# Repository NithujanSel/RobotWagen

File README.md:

# RobotWagen
SmartSytems Project

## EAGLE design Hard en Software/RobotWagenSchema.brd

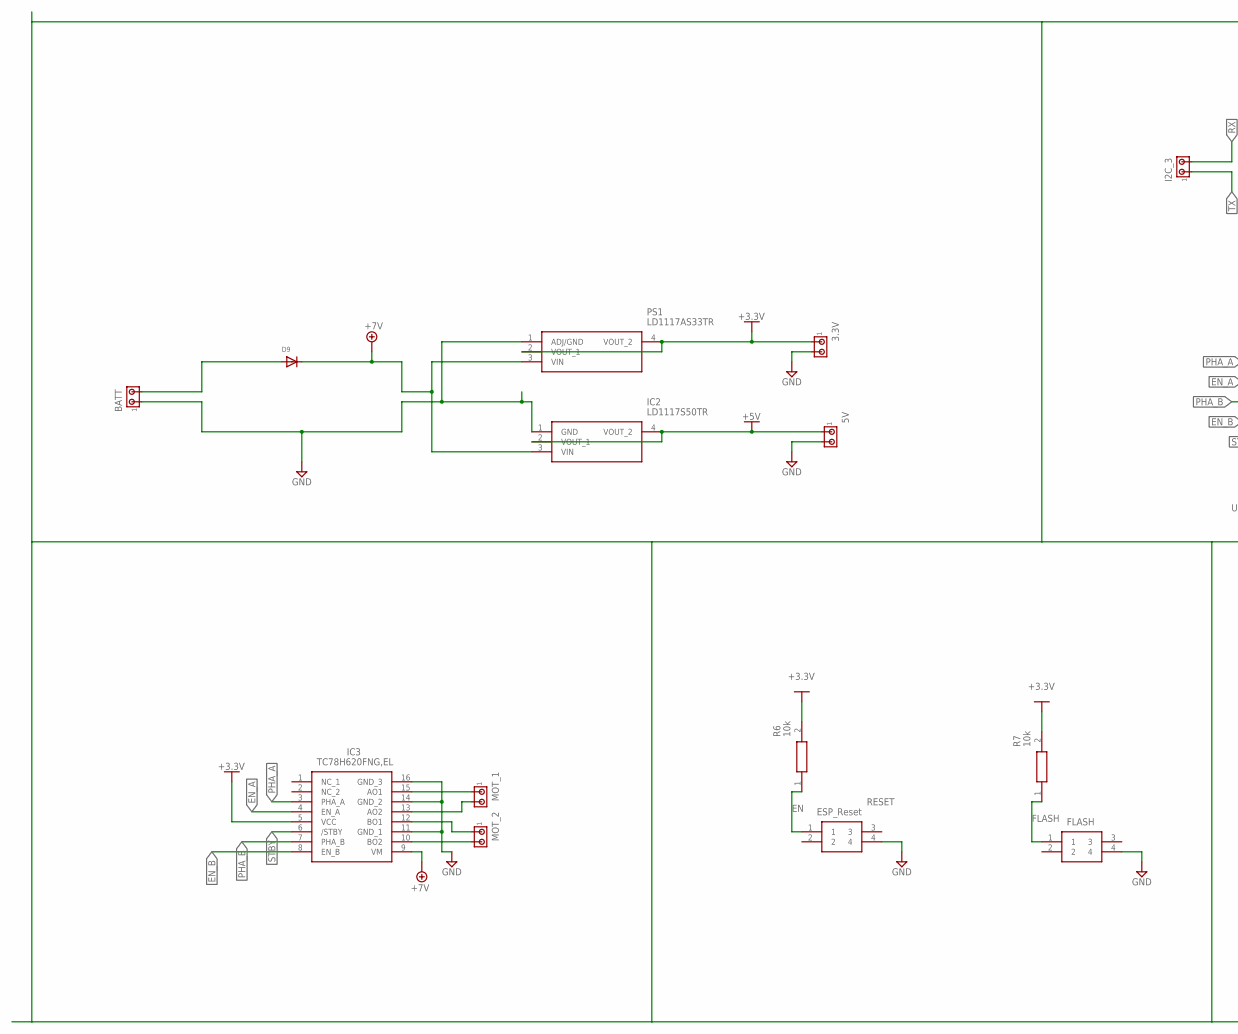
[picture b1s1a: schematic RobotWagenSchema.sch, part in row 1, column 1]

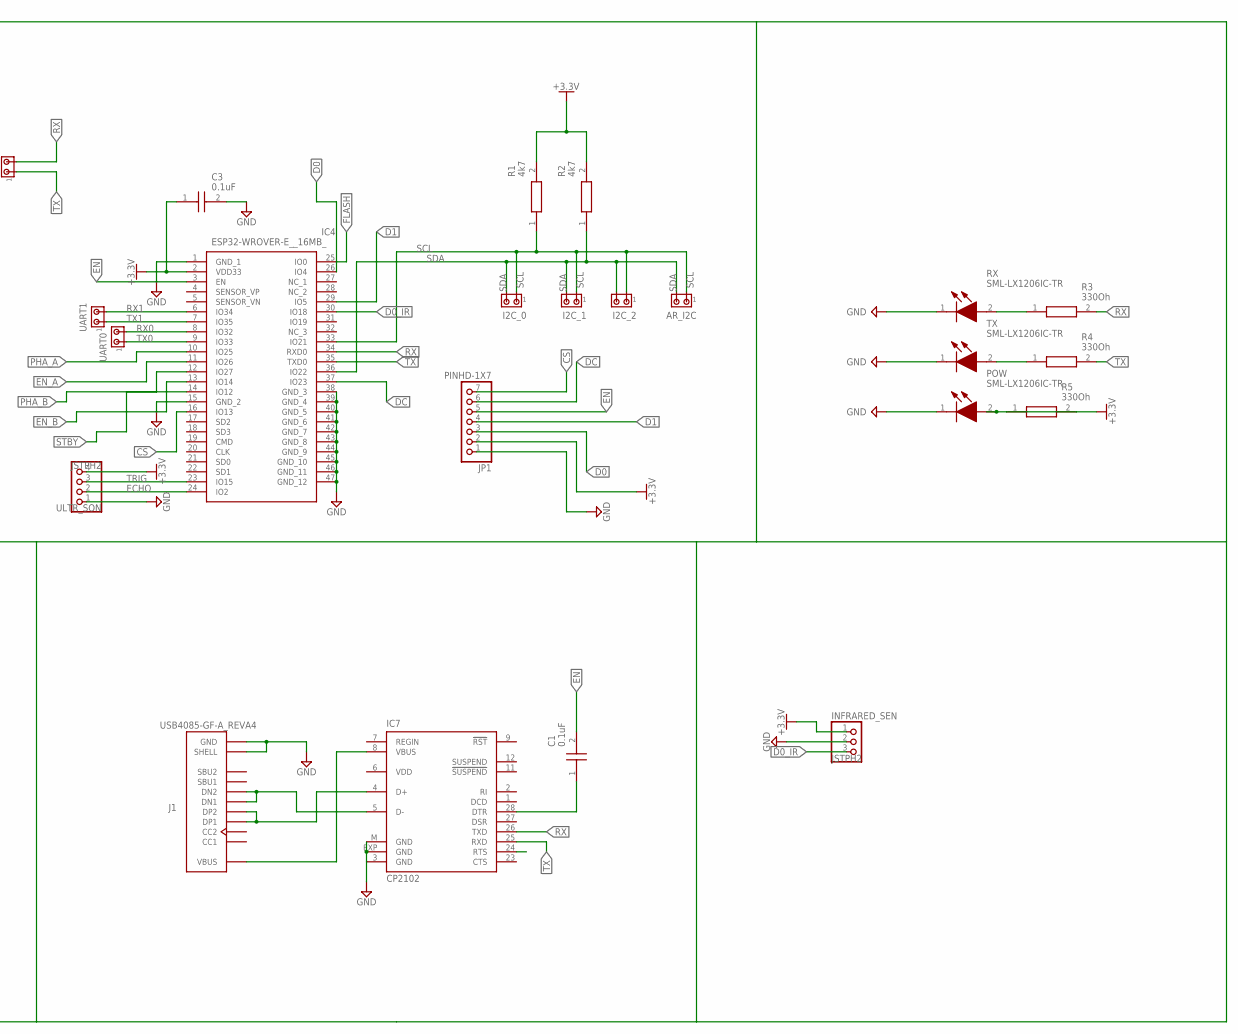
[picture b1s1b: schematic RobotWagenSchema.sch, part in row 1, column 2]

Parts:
3.3V, 5V: MTA02-156; 1X2MTA
AR_I2C: MTA02-156; 1X2MTA
BATT: MTA02-156; 1X2MTA
C1, C3: 0.1uF; CAPC2012X145N
D9: DIODESMA; SMADIODE
FLASH: ESP_FL; 430182070816
I2C_0, I2C_1, I2C_2, I2C_3: MTA02-156; 1X2MTA
IC2: LD1117S50TR; SOT230P700X190-4N
IC3: TC78H620FNG,EL; SOP65P640X160-16N
IC4: ESP32-WROVER-E__16MB_; ESP32WROVERE16MB
IC7: CP2102; MLP28
INFRARED_SEN: JSTPH2
J1: USB4085-GF-A_REVA4; GCT_USB4085-GF-A_REVA4
JP1: PINHD-1X7; 1X07
MOT_1, MOT_2: MTA02-156; 1X2MTA
POW: SML-LX1206IC-TR; SMLLX1206ICTR
PS1: LD1117AS33TR; SOT230P700X190-4N
R1, R2: 4k7; RESC2012X65N
R3, R4, R5: 330Oh; RESC2012X65N
R6, R7: 10k; RESC2012X65N
RESET: ESP_Reset; 430182070816
RX: SML-LX1206IC-TR; SMLLX1206ICTR
TX: SML-LX1206IC-TR; SMLLX1206ICTR
UART0, UART1: MTA02-156; 1X2MTA
ULTR_SON: JSTPH2

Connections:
+3.3V: 3.3V.1, C3.1, IC3.5 (VCC), IC4.2 (VDD33), INFRARED_SEN.1, JP1.2, POW.2 (A), PS1.2 (VOUT_1), PS1.4 (VOUT_2), R1.2, R2.2, R5.1, R5.2, R6.2, R7.2, ULTR_SON.4
+5V: 5V.1, IC2.2 (VOUT_1), IC2.4 (VOUT_2)
+7V: D9.C, IC2.3 (VIN), IC3.9 (VM), PS1.3 (VIN)
CS: IC4.16 (IO13), JP1.7
D0: IC4.26 (IO4), JP1.3
D0_IR: IC4.30 (IO18), INFRARED_SEN.3
D1: IC4.29 (IO5), JP1.4
DC: IC4.37 (IO23), JP1.6
ECHO: IC4.24 (IO2), ULTR_SON.2
EN: C1.2, IC4.3 (EN), JP1.5, R6.1, RESET.1
EN_A: IC3.4 (EN_A), IC4.11 (IO26)
EN_B: IC3.8 (EN_B), IC4.13 (IO14)
FLASH: FLASH.1, IC4.25 (IO0), R7.1
GND: 3.3V.2, 5V.2, BATT.1, C3.2, FLASH.4, IC2.1 (GND), IC3.11 (GND_1), IC3.14 (GND_2), IC3.16 (GND_3), IC4.1 (GND_1), IC4.15 (GND_2), IC4.38 (GND_3), IC4.39 (GND_4), IC4.40 (GND_5), IC4.41 (GND_6), IC4.42 (GND_7), IC4.43 (GND_8), IC4.44 (GND_9), IC4.45 (GND_10), IC4.46 (GND_11), IC4.47 (GND_12), IC7.3 (GND), IC7.EXP (GND), IC7.M (GND), INFRARED_SEN.2, J1.A1 (GND), J1.A12 (GND), J1.B1 (GND), J1.B12 (GND), J1.P1 (SHELL), J1.P2 (SHELL), J1.P3 (SHELL), J1.P4 (SHELL), JP1.1, POW.1 (K), PS1.1 (ADJ/GND), RESET.4, RX.1 (K), TX.1 (K), ULTR_SON.1
unnamed: BATT.2, D9.A
unnamed: C1.1, IC7.28 (DTR)
unnamed: IC3.15 (AO1), MOT_1.1
unnamed: IC3.13 (AO2), MOT_1.2
unnamed: IC7.5 (D-), J1.A7 (DN1), J1.B7 (DN2)
unnamed: IC3.10 (BO2), MOT_2.2
unnamed: IC3.12 (BO1), MOT_2.1
unnamed: R3.1, RX.2 (A)
unnamed: IC7.4 (D+), J1.A6 (DP1), J1.B6 (DP2)
unnamed: IC7.8 (VBUS), J1.A4 (VBUS), J1.A9 (VBUS), J1.B4 (VBUS), J1.B9 (VBUS)
PHA_A: IC3.3 (PHA_A), IC4.10 (IO25)
PHA_B: IC3.7 (PHA_B), IC4.12 (IO27)
RX: I2C_3.2, IC4.34 (RXD0), IC7.26 (TXD), R3.2
RX0: IC4.8 (IO32), UART0.2
RX1: IC4.6 (IO34), UART1.2
SCL: AR_I2C.1, I2C_0.1, I2C_1.1, I2C_2.1, IC4.33 (IO21), R1.1
SDA: AR_I2C.2, I2C_0.2, I2C_1.2, I2C_2.2, IC4.36 (IO22), R2.1
STBY: IC3.6 (/STBY), IC4.14 (IO12)
TRIG: IC4.23 (IO15), ULTR_SON.3
TX: I2C_3.1, IC4.35 (TXD0), IC7.25 (RXD), R4.1, R4.2, TX.2 (A)
TX0: IC4.9 (IO33), UART0.1
TX1: IC4.7 (IO35), UART1.1
VDD: IC7.6 (VDD)

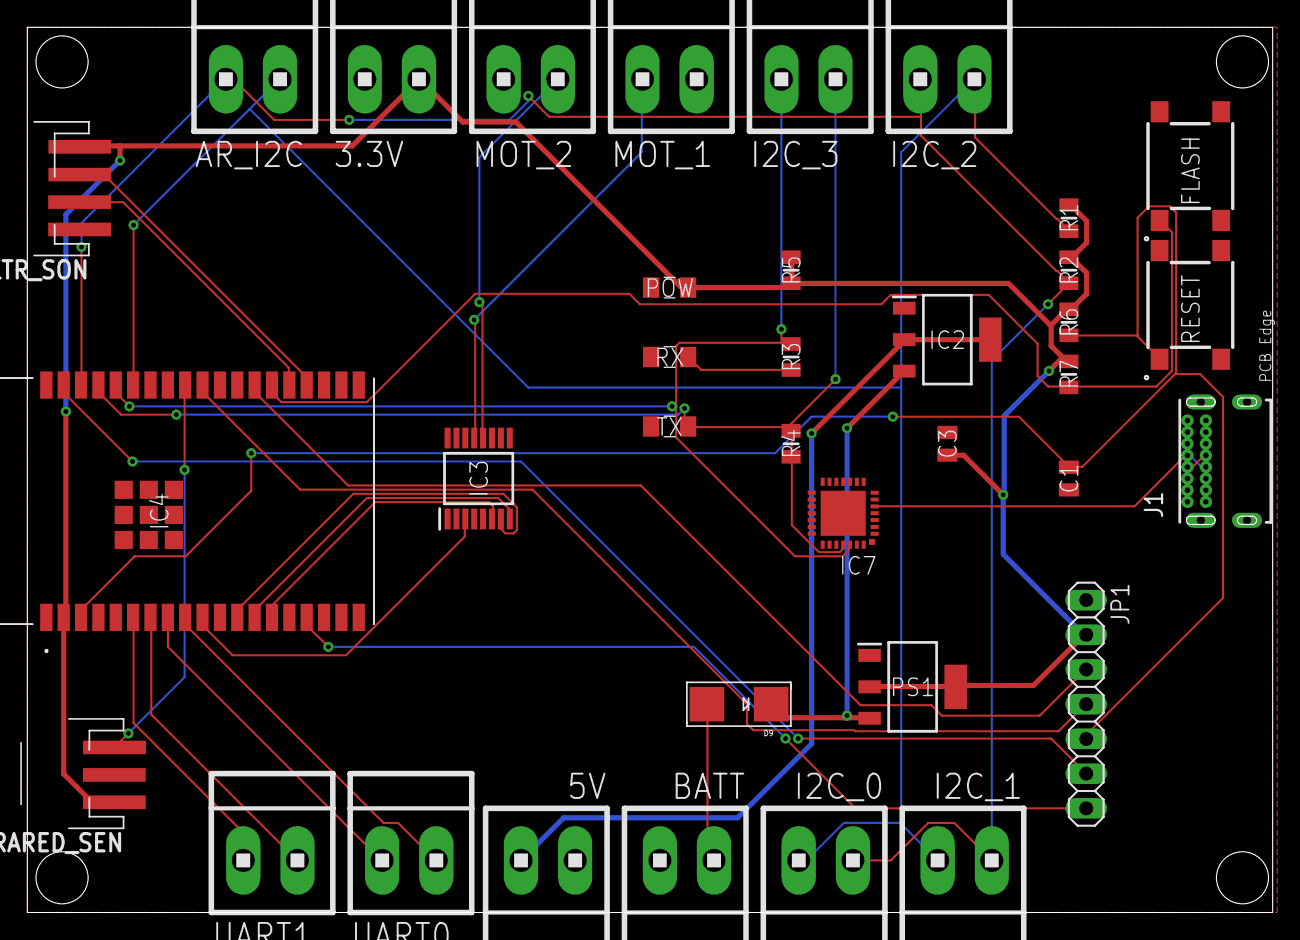
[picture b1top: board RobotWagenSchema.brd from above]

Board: 2 copper layers, 91.1 x 64.8 mm, 36 parts (0 on the bottom side), 36 nets.

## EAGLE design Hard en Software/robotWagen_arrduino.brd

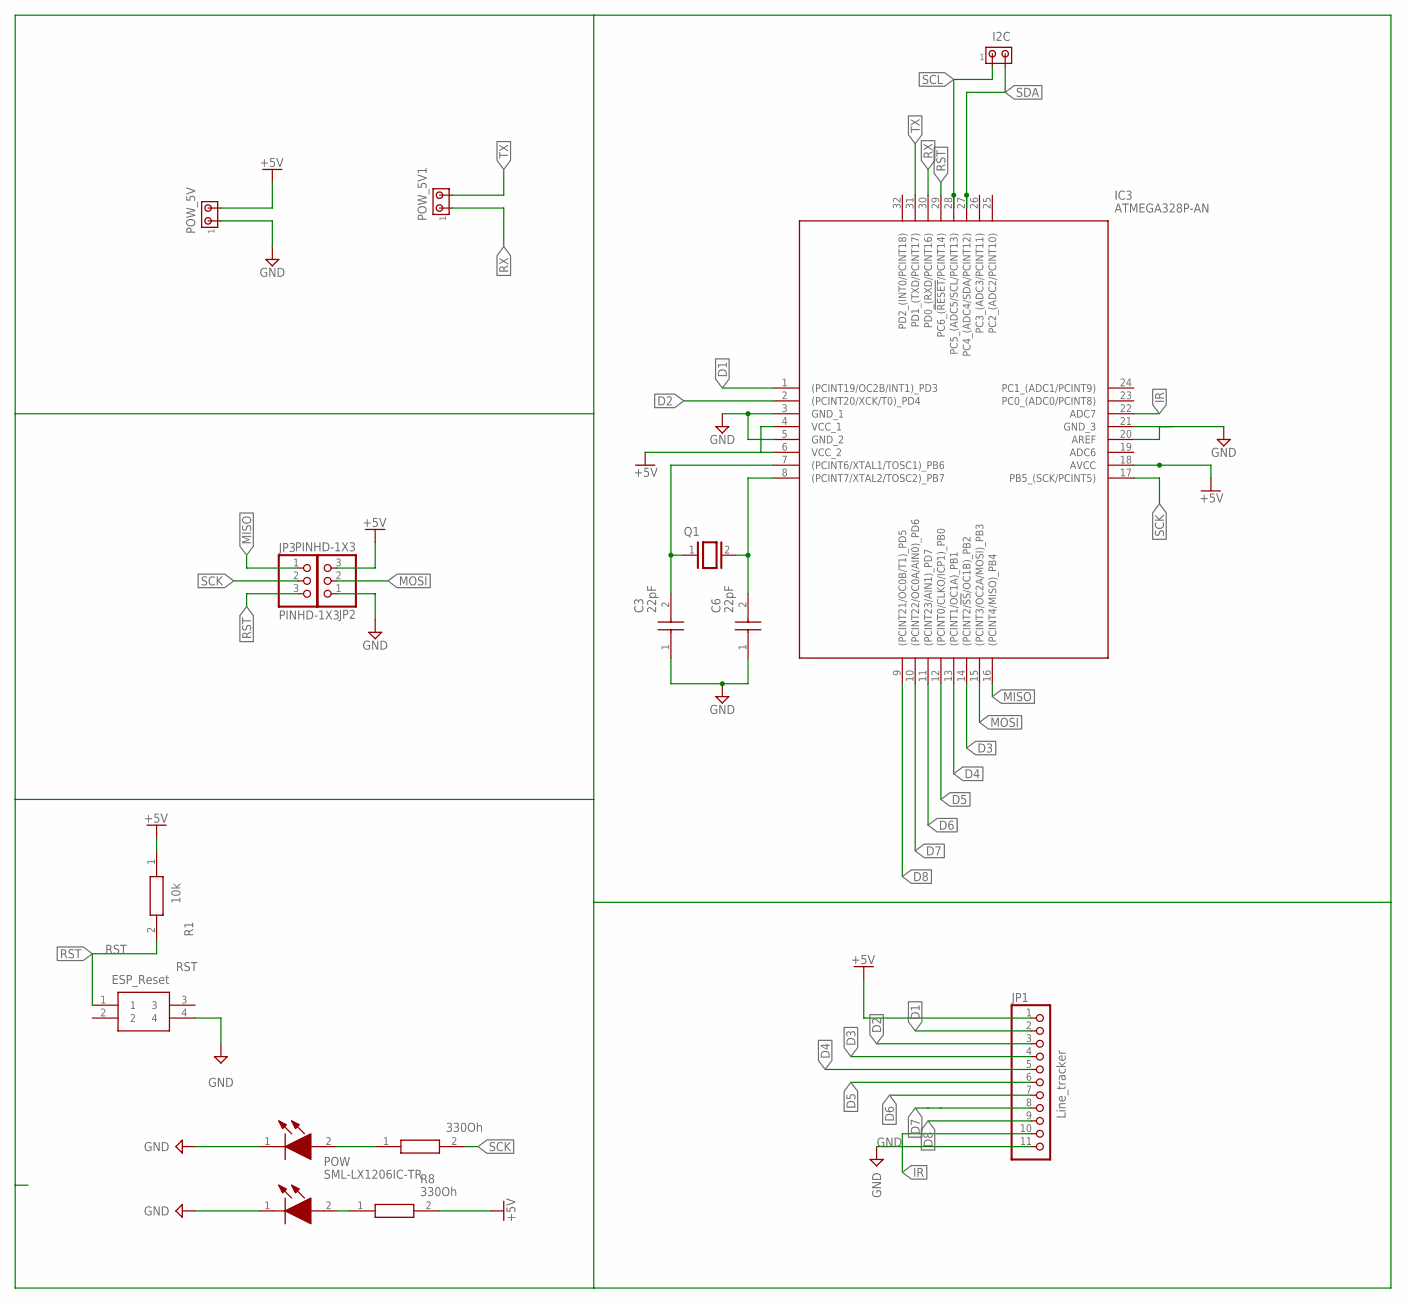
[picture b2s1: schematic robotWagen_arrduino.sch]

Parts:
C3, C6: 22pF; CAPC2012X145N
I2C: MTA02-156; 1X2MTA
IC3: ATMEGA328P-AN; QFP80P900X900X120-32N
JP1: Line_tracker; 1X11
JP2, JP3: PINHD-1X3; 1X03
POW: SML-LX1206IC-TR; SMLLX1206ICTR
POW_5V, POW_5V1: MTA02-156; 1X2MTA
Q1: XTAL/S; QS
R1: 10k; RESC2012X65N
R7, R8: 330Oh; RESC2012X65N
RST: ESP_Reset; 430182070816
TX: SML-LX1206IC-TR; SMLLX1206ICTR

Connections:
+5V: IC3.4 (VCC_1), IC3.6 (VCC_2), IC3.18 (AVCC), JP1.1, JP2.3, POW_5V.2, R1.1, R8.2
D1: IC3.1 ((PCINT19/OC2B/INT1)_PD3), JP1.2
D2: IC3.2 ((PCINT20/XCK/T0)_PD4), JP1.3
D3: IC3.14 ((PCINT2/!SS!/OC1B)_PB2), JP1.4
D4: IC3.13 ((PCINT1/OC1A)_PB1), JP1.5
D5: IC3.12 ((PCINT0/CLKO/ICP1)_PB0), JP1.6
D6: IC3.11 ((PCINT23/AIN1)_PD7), JP1.7
D7: IC3.10 ((PCINT22/OC0A/AIN0)_PD6), JP1.8
D8: IC3.9 ((PCINT21/OC0B/T1)_PD5), JP1.9
GND: C3.1, C6.1, IC3.3 (GND_1), IC3.5 (GND_2), IC3.20 (AREF), IC3.21 (GND_3), JP1.11, JP2.1, POW.1 (K), POW_5V.1, RST.4, TX.1 (K)
IR: IC3.22 (ADC7), JP1.10
MISO: IC3.16 ((PCINT4/MISO)_PB4), JP3.1
MOSI: IC3.15 ((PCINT3/OC2A/MOSI)_PB3), JP2.2
unnamed: POW.2 (A), R8.1
unnamed: C3.2, IC3.7 ((PCINT6/XTAL1/TOSC1)_PB6), Q1.1
unnamed: C6.2, IC3.8 ((PCINT7/XTAL2/TOSC2)_PB7), Q1.2
RST: IC3.29 (PC6_(!RESET!/PCINT14)), JP3.3, R1.2, RST.1
RX: IC3.30 (PD0_(RXD/PCINT16)), POW_5V1.1
SCK: IC3.17 (PB5_(SCK/PCINT5)), JP3.2, R7.2
SCL: I2C.1, IC3.28 (PC5_(ADC5/SCL/PCINT13))
SDA: I2C.2, IC3.27 (PC4_(ADC4/SDA/PCINT12))
TX: IC3.31 (PD1_(TXD/PCINT17)), POW_5V1.2
TX1: R7.1, TX.2 (A)

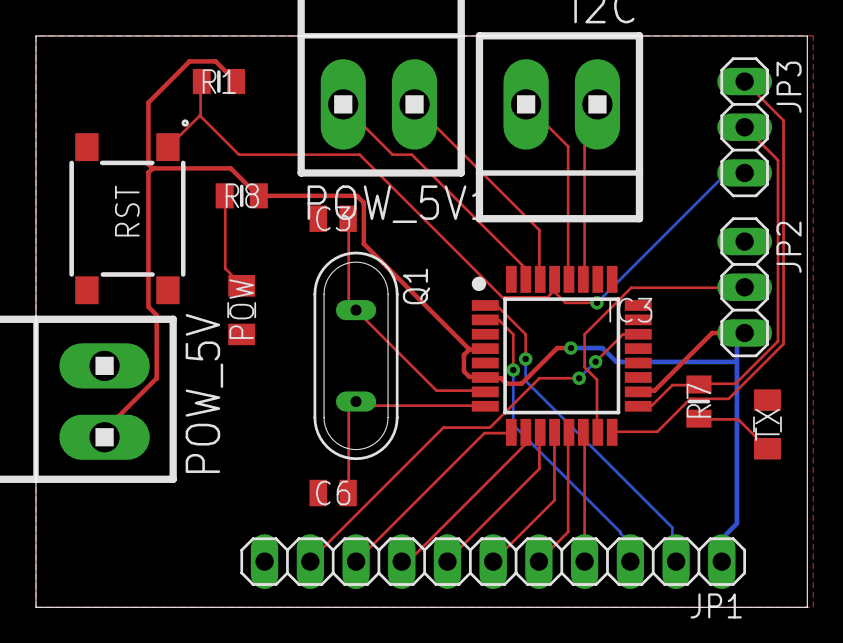
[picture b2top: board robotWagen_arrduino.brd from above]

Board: 2 copper layers, 42.9 x 31.7 mm, 16 parts (0 on the bottom side), 23 nets.

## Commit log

2022-03-11 Bestanden aangemaakt
2022-03-18 Eerste versie verslag
2022-03-18 gitingonor
2022-06-16 finale1
2022-06-16 finale2
2022-06-16 finale3
2022-06-16 finale5
